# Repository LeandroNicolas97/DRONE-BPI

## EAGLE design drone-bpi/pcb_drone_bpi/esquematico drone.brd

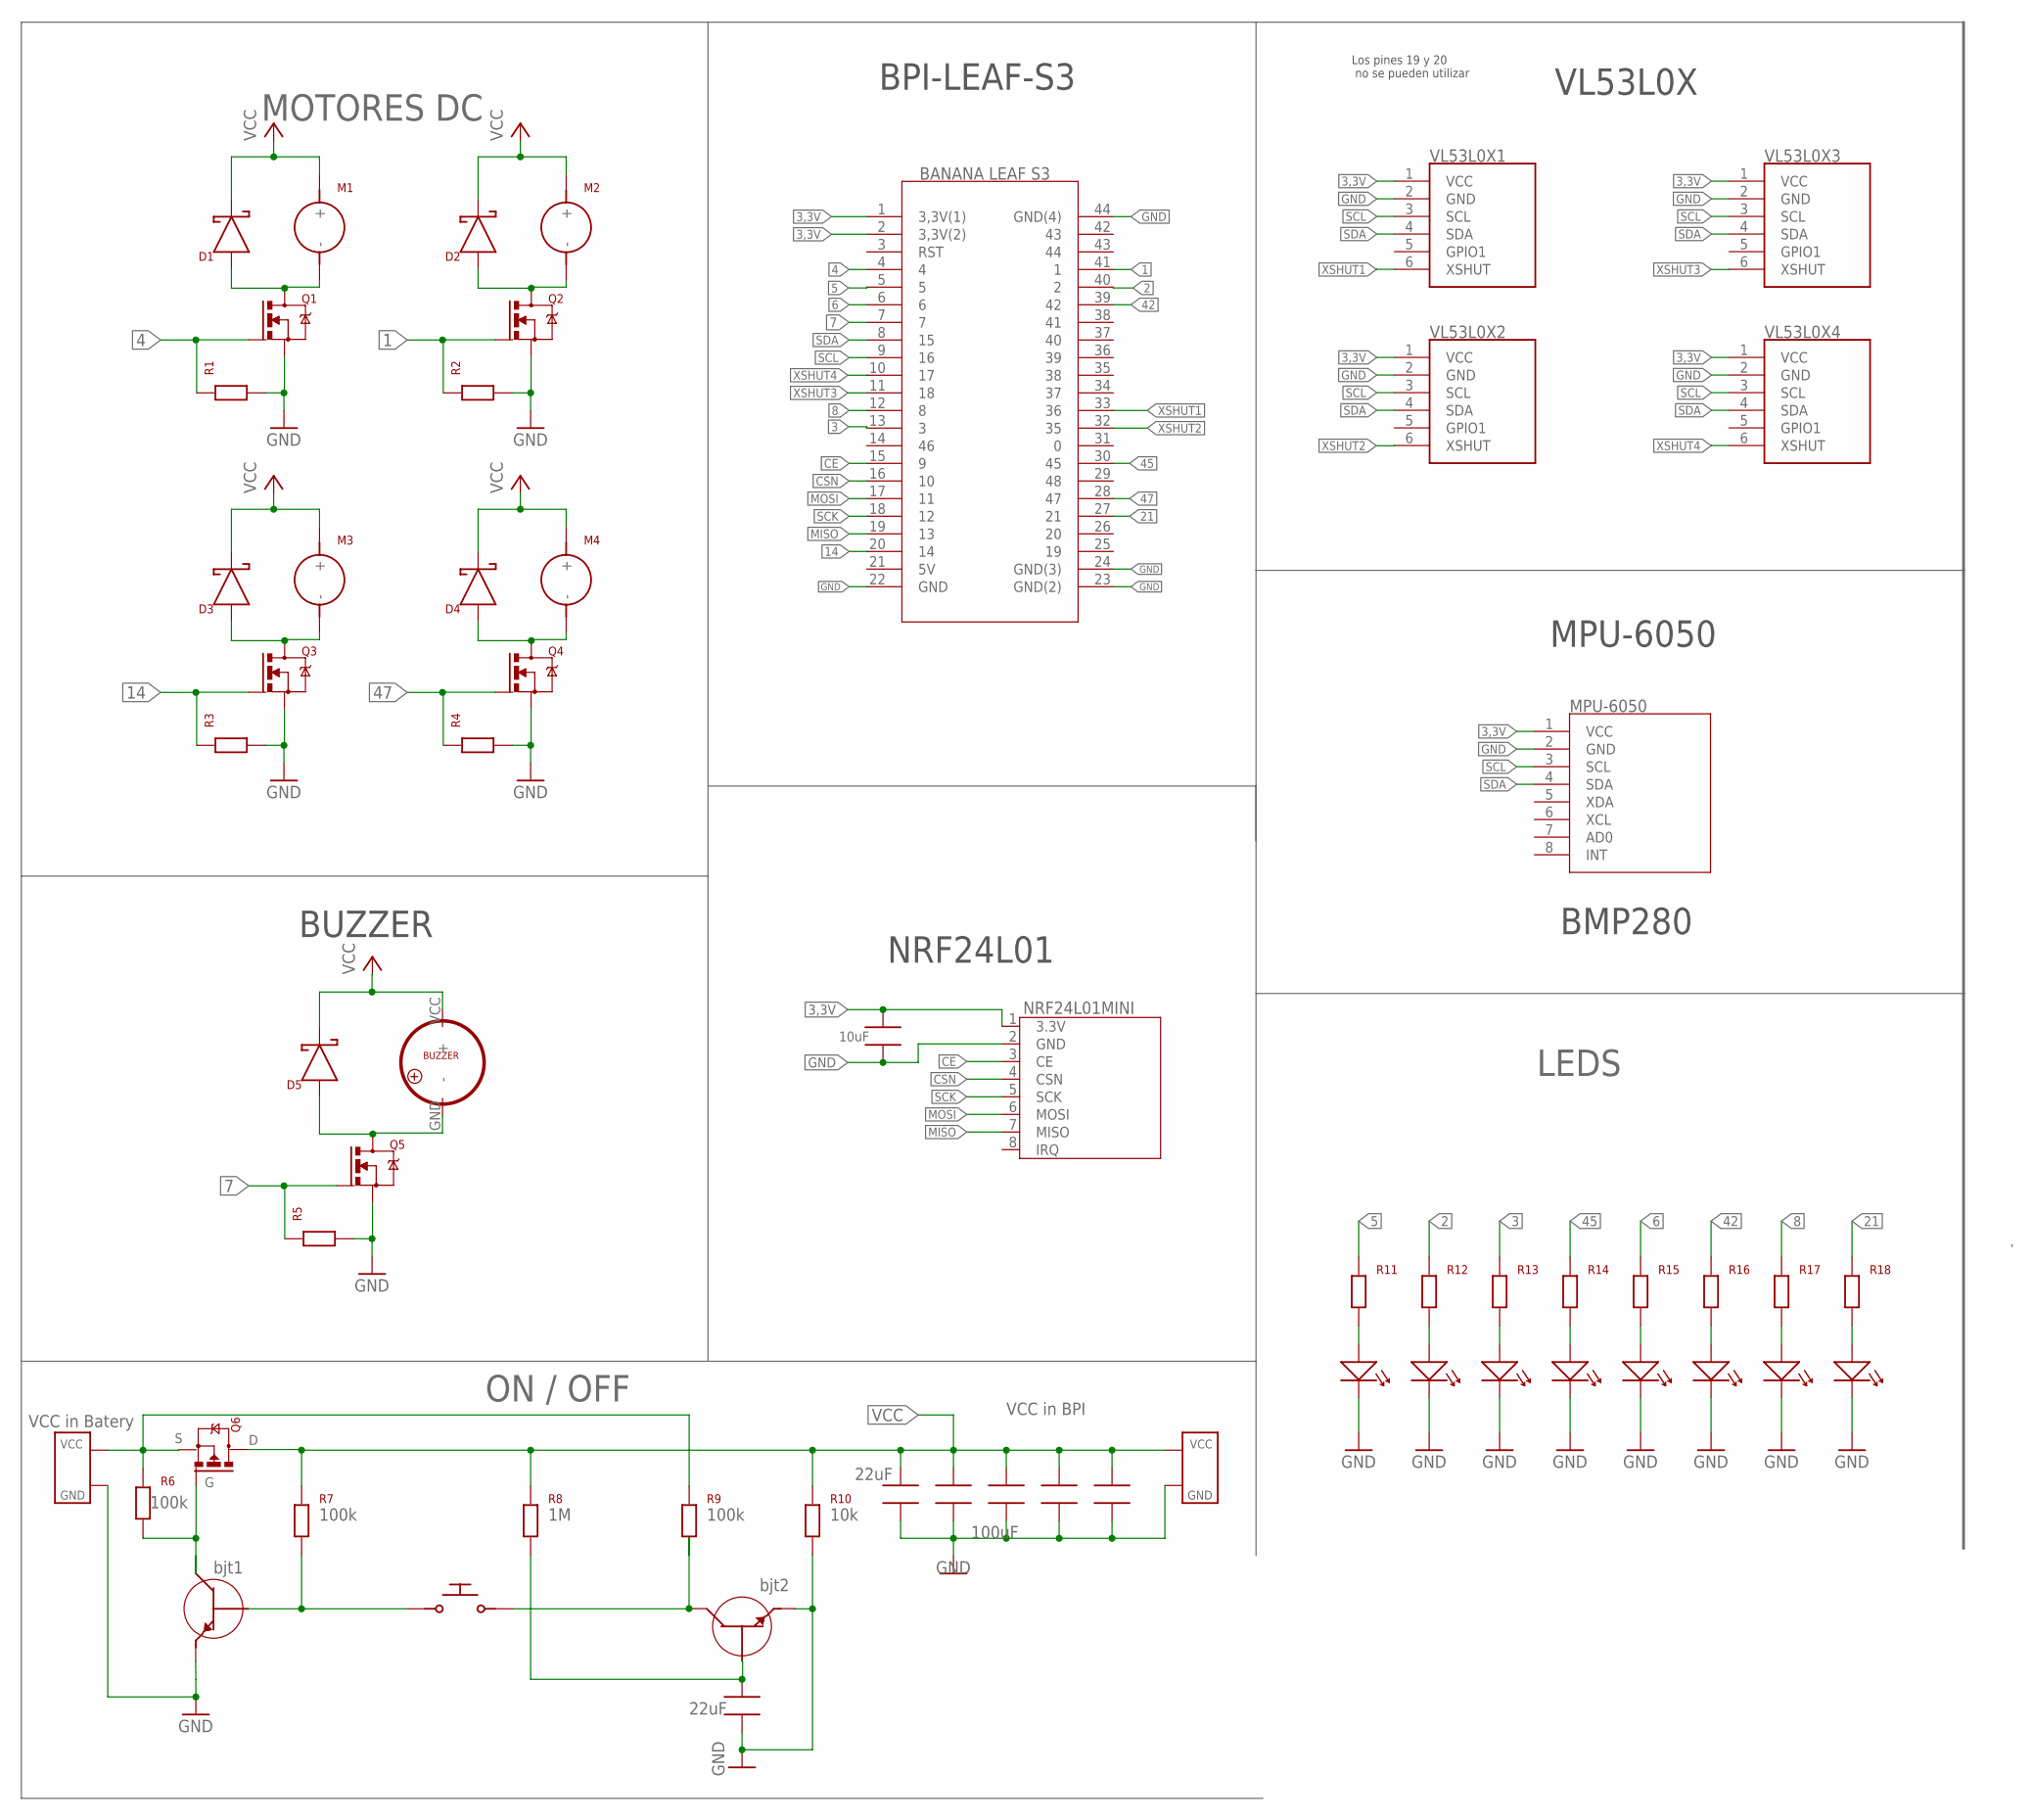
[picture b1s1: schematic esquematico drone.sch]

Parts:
BANANALEAFS1: BANANALEAFS3; BANANALEAF
BAT1, BAT2: BATBAT; BAT
BJT1, BJT2: MMBT3904
C1, C3: 100uF; CAPACITOR-100UF
C2, C7: CAPACITOR-22UF
C4, C5, C6: CAPACITOR-100UFCAPACITOR; CAPACITOR-100UF
D1, D2, D3, D4, D5: SS12
LED1, LED2, LED3, LED4, LED5, LED6, LED7, LED8: LEDS
M1, M2, M3, M4: MOTORM; MOTOR
MPU1: MPU6050MPU6050; MPU6050
NRF24L1: NRF24L01MINI
P1: PULSADOR
Q1, Q2, Q3, Q4, Q5: SI2302
Q6: SI2301SI2301; SI2301
R1, R2, R3, R4, R5, R6, R7, R8, R9, R10, R11, R12, R13, R14, R15, R16, R17, R18: RESISTOR-0805
U$2: BUZZER
VL53L0X1, VL53L0X2, VL53L0X3, VL53L0X4: VL53L0X

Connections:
1: BANANALEAFS1.41 (1), Q2.G, R2.S1
2: BANANALEAFS1.40 (2), R12.S1
3: BANANALEAFS1.13 (3), R13.S1
3,3V: BANANALEAFS1.1 (3,3V(1)), BANANALEAFS1.2 (3,3V(2)), C7.S1 (C1), MPU1.1 (VCC), NRF24L1.1 (3.3V), VL53L0X1.1 (VCC), VL53L0X2.1 (VCC), VL53L0X3.1 (VCC), VL53L0X4.1 (VCC)
4: BANANALEAFS1.4, Q1.G, R1.S1
5: BANANALEAFS1.5, R11.S1
6: BANANALEAFS1.6, R15.S1
7: BANANALEAFS1.7, Q5.G, R5.S1
8: BANANALEAFS1.12 (8), R17.S1
14: BANANALEAFS1.20 (14), Q3.G, R3.S1
21: BANANALEAFS1.27 (21), R18.S1
42: BANANALEAFS1.39 (42), R16.S1
45: BANANALEAFS1.30 (45), R14.S1
47: BANANALEAFS1.28 (47), Q4.G, R4.S1
CE: BANANALEAFS1.15 (9), NRF24L1.3 (CE)
CSN: BANANALEAFS1.16 (10), NRF24L1.4 (CSN)
GND: BANANALEAFS1.22 (GND), BANANALEAFS1.23 (GND(2)), BANANALEAFS1.24 (GND(3)), BANANALEAFS1.44 (GND(4)), BAT1.GND, BAT2.GND, BJT1.E, BJT2.E, C1.C2, C2.S2 (C2), C3.C2, C4.C2, C5.C2, C6.C2, C7.S2 (C2), LED1.C, LED2.C, LED3.C, LED4.C, LED5.C, LED6.C, LED7.C, LED8.C, MPU1.2 (GND), NRF24L1.2 (GND), Q1.S, Q2.S, Q3.S, Q4.S, Q5.S, R1.S2, R2.S2, R3.S2, R4.S2, R5.S2, R10.S2, VL53L0X1.2 (GND), VL53L0X2.2 (GND), VL53L0X3.2 (GND), VL53L0X4.2 (GND)
MISO: BANANALEAFS1.19 (13), NRF24L1.7 (MISO)
MOSI: BANANALEAFS1.17 (11), NRF24L1.6 (MOSI)
unnamed: D1.A, M1.-, Q1.D
unnamed: LED1.A, R11.S2
unnamed: D2.A, M2.-, Q2.D
unnamed: D3.A, M3.-, Q3.D
unnamed: BAT2.VCC, Q6.S, R6.S1, R9.S1
unnamed: BJT1.C, Q6.G, R6.S2
unnamed: D5.A, Q5.D, U$2.GND (-)
unnamed: LED2.A, R12.S2
unnamed: BJT1.B, P1.P1 (1), R7.S2
unnamed: BJT2.C, P1.P2 (2), R9.S2
unnamed: BJT2.B, C2.S1 (C1), R8.S2
unnamed: LED3.A, R13.S2
unnamed: LED4.A, R14.S2
unnamed: LED5.A, R15.S2
unnamed: LED6.A, R16.S2
unnamed: D4.A, M4.-, Q4.D
unnamed: LED7.A, R17.S2
unnamed: LED8.A, R18.S2
SCK: BANANALEAFS1.18 (12), NRF24L1.5 (SCK)
SCL: BANANALEAFS1.9 (16), MPU1.3 (SCL), VL53L0X1.3 (SCL), VL53L0X2.3 (SCL), VL53L0X3.3 (SCL), VL53L0X4.3 (SCL)
SDA: BANANALEAFS1.8 (15), MPU1.4 (SDA), VL53L0X1.4 (SDA), VL53L0X2.4 (SDA), VL53L0X3.4 (SDA), VL53L0X4.4 (SDA)
VCC: BAT1.VCC, C1.C1, C3.C1, C4.C1, C5.C1, C6.C1, D1.C, D2.C, D3.C, D4.C, D5.C, M1.+, M2.+, M3.+, M4.+, Q6.D, R7.S1, R8.S1, R10.S1, U$2.VCC (+)
XSHUT1: BANANALEAFS1.33 (36), VL53L0X1.6 (XSHUT)
XSHUT2: BANANALEAFS1.32 (35), VL53L0X2.6 (XSHUT)
XSHUT3: BANANALEAFS1.11 (18), VL53L0X3.6 (XSHUT)
XSHUT4: BANANALEAFS1.10 (17), VL53L0X4.6 (XSHUT)

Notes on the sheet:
MOTORES DC
BPI-LEAF-S3
NRF24L01
MPU-6050
BMP280
VL53L0X
BUZZER
LEDS
ON / OFF
VCC in Batery
100k
10k
22uF
100uF
VCC in BPI
bjt1
bjt2
Los pines 19 y 20 no se pueden utilizar
10uF

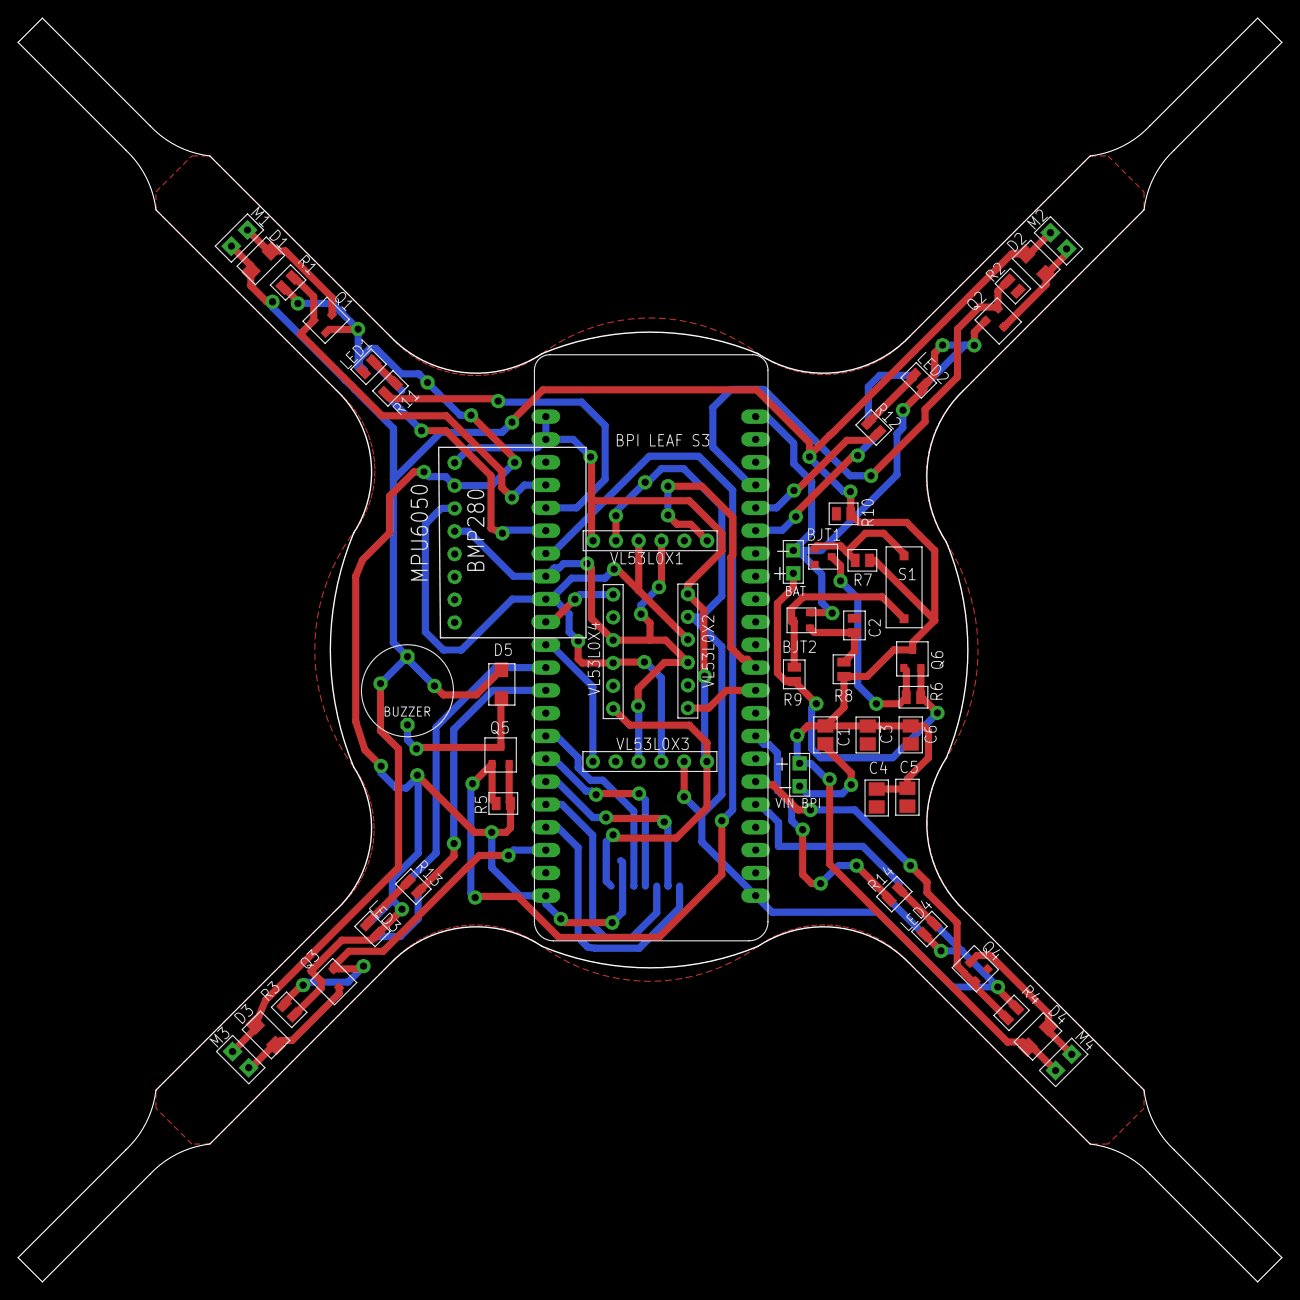
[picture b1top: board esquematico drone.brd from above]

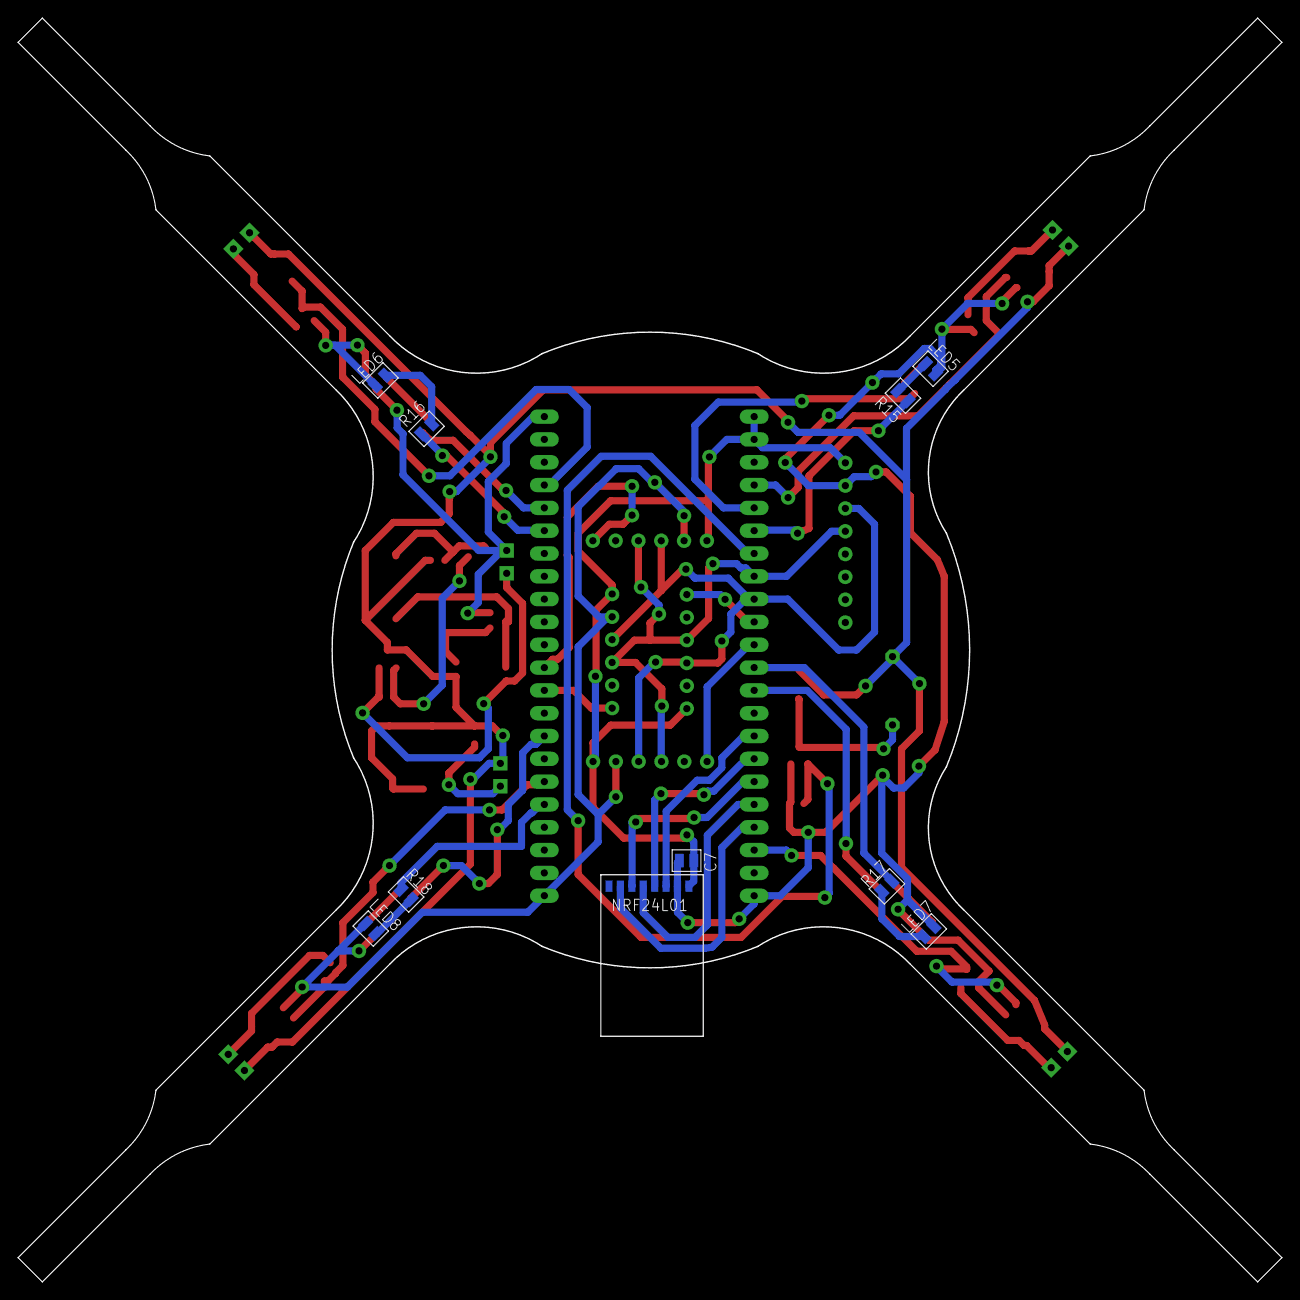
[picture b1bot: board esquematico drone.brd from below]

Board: 2 copper layers, 140.6 x 140.6 mm, 61 parts (10 on the bottom side), 45 nets.

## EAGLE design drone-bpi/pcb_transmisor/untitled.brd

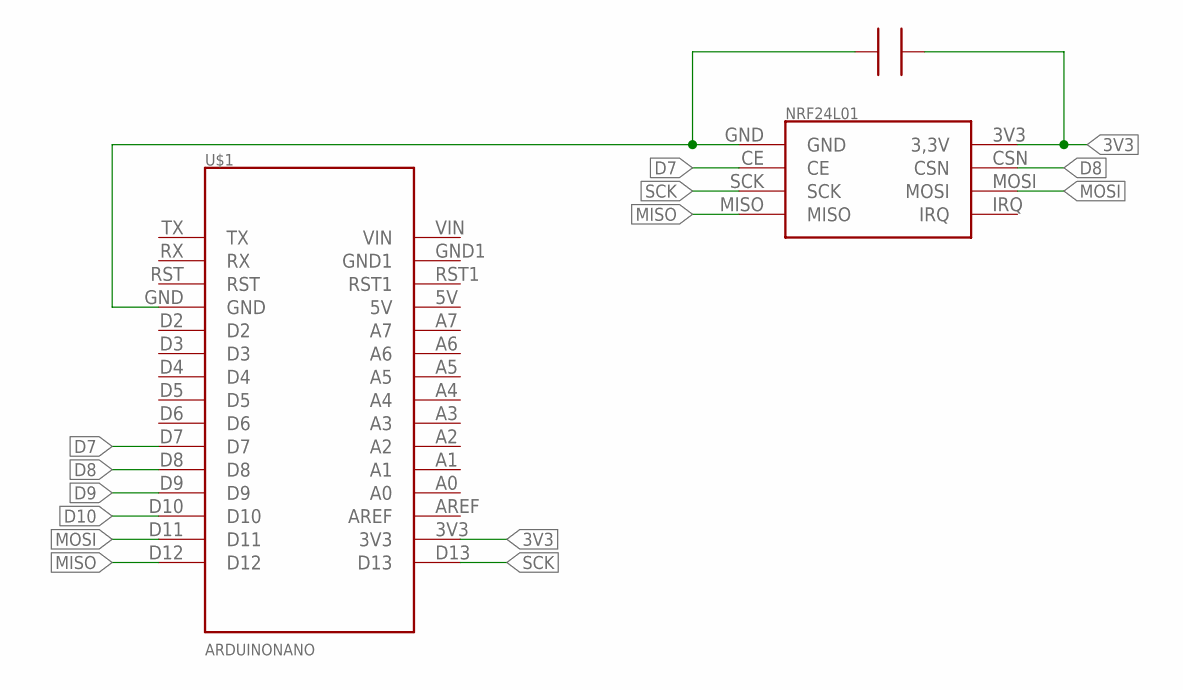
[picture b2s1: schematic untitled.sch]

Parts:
U$1: ARDUINONANO
U$2: C
U$3: NRF24L01

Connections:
3V3: U$1.3V3, U$2.+, U$3.3V3 (3,3V)
D7: U$1.D7, U$3.CE
D8: U$1.D8, U$3.CSN
D9: U$1.D9
D10: U$1.D10
MISO: U$1.D12, U$3.MISO
MOSI: U$1.D11, U$3.MOSI
unnamed: U$1.GND, U$2.-, U$3.GND
SCK: U$1.D13, U$3.SCK

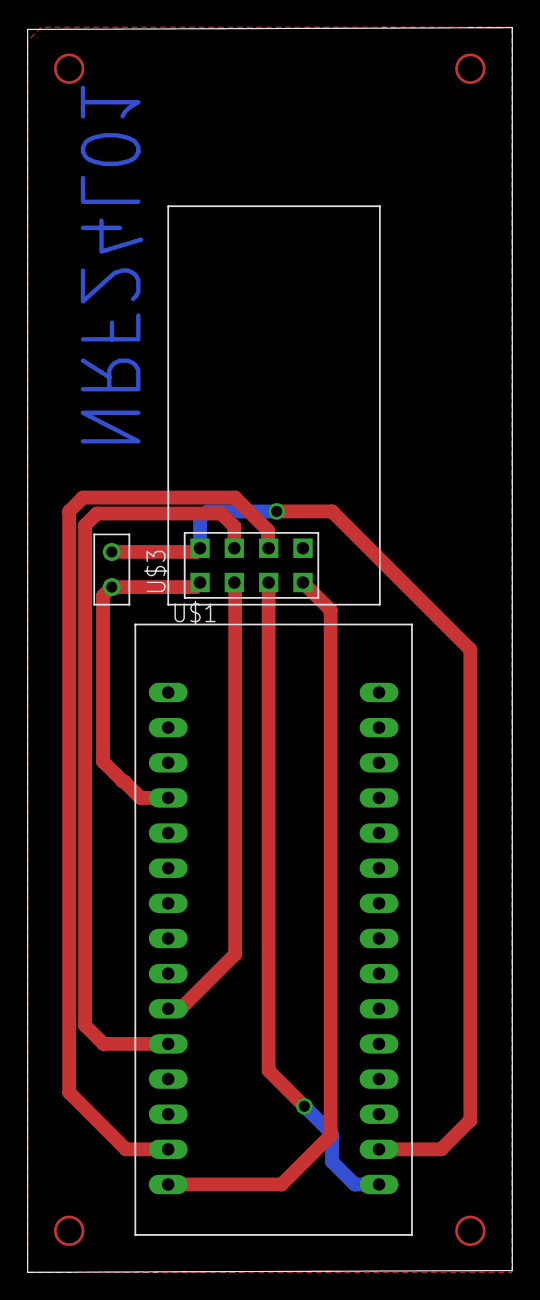
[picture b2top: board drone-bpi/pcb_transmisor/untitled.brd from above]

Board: 2 copper layers, 35.0 x 90.0 mm, 3 parts (0 on the bottom side), 7 nets.

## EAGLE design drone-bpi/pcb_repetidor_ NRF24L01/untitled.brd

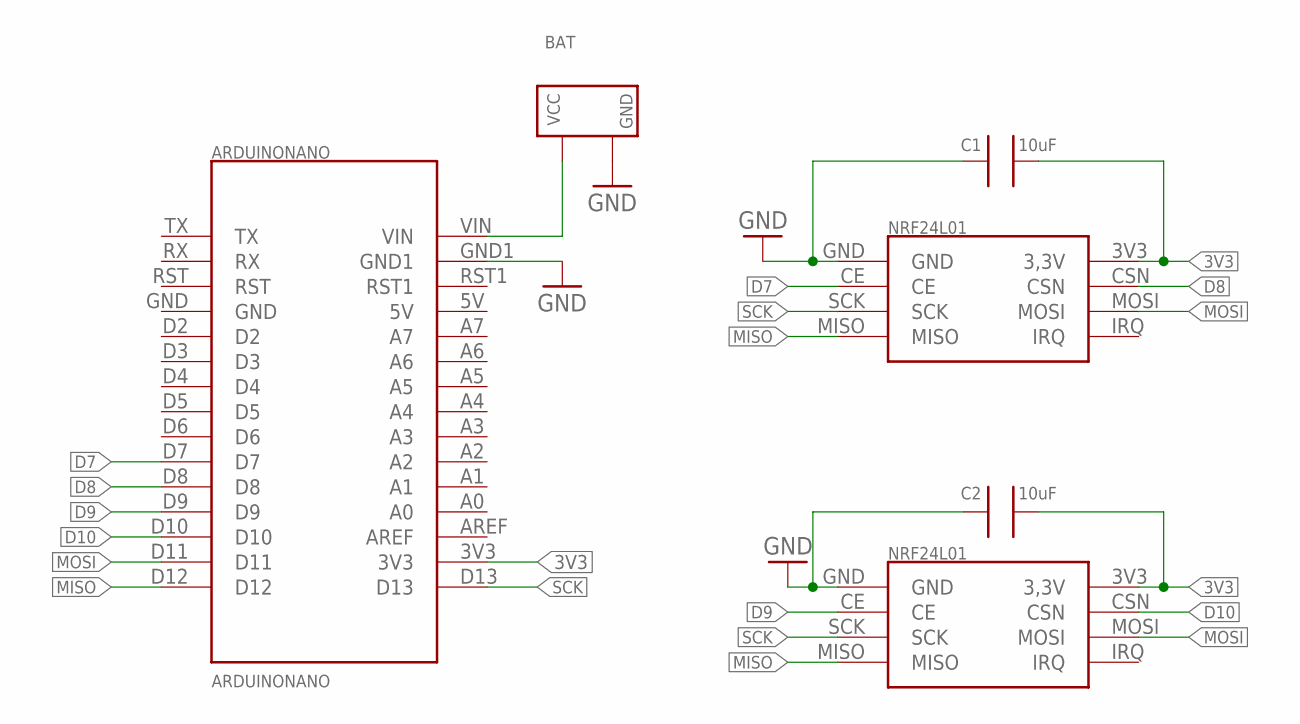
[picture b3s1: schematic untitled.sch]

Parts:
ARDUINONANO: ARDUINONANO
BAT1: BATBAT; BAT
C1, C2: NRF24L01
U$3, U$4: C

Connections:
3V3: ARDUINONANO.3V3, C1.3V3 (3,3V), C2.3V3 (3,3V), U$3.+, U$4.+
D7: ARDUINONANO.D7, C2.CE
D8: ARDUINONANO.D8, C2.CSN
D9: ARDUINONANO.D9, C1.CE
D10: ARDUINONANO.D10, C1.CSN
GND: ARDUINONANO.GND1, BAT1.GND, C1.GND, C2.GND, U$3.-, U$4.-
MISO: ARDUINONANO.D12, C1.MISO, C2.MISO
MOSI: ARDUINONANO.D11, C1.MOSI, C2.MOSI
unnamed: ARDUINONANO.VIN, BAT1.VCC
SCK: ARDUINONANO.D13, C1.SCK, C2.SCK

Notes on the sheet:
10uF
BAT

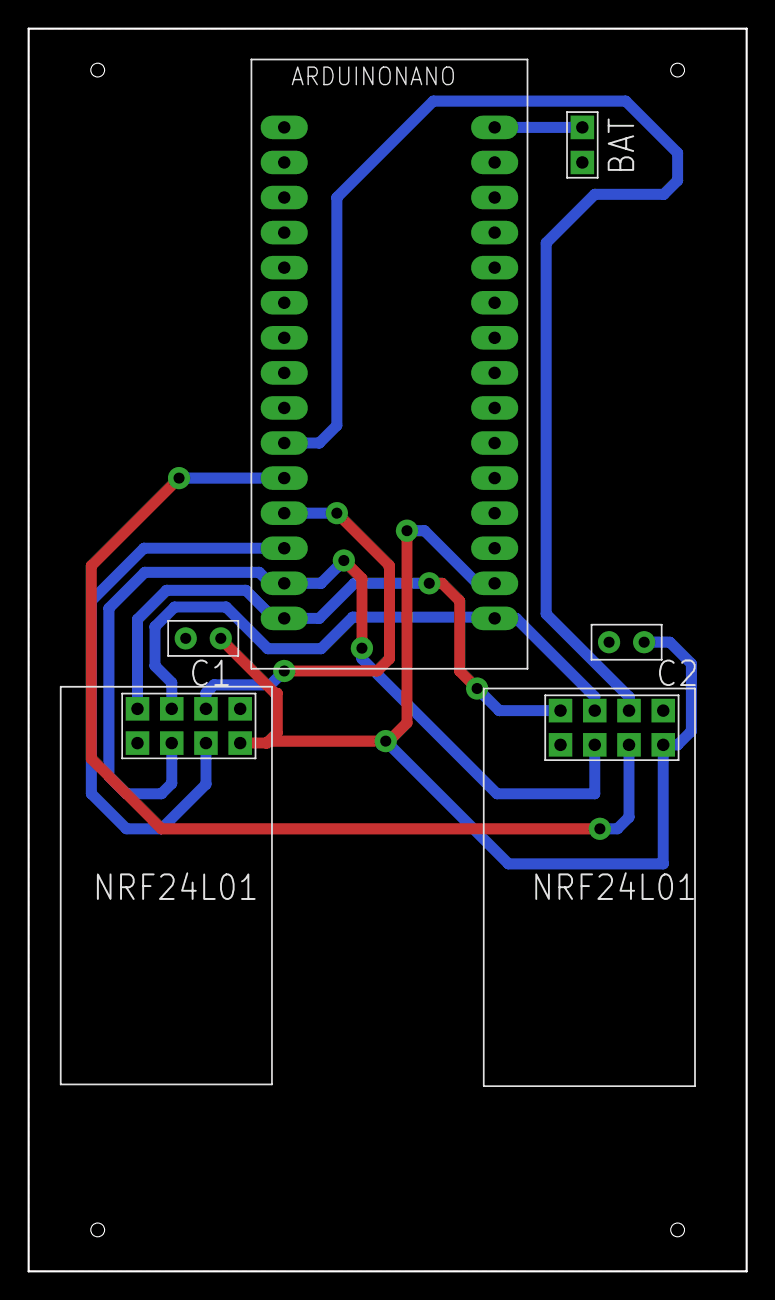
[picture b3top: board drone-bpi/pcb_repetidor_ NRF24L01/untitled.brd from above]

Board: 2 copper layers, 52.0 x 90.0 mm, 6 parts (0 on the bottom side), 10 nets.

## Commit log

2025-03-16 Drone files and code
2025-03-16 Added code drone
